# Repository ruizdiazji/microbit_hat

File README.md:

## Placa de expansión para utilizar con MICROBIT    

### Descripción y contexto
---

Esta placa, también llamada "shield" o "hat" en el mundo maker, permite tener acceso a todos los pines de entrada salida de la micro:bit. Además tiene incorporado un IC que permite cargar de forma autónoma una celda 18650 de ion-litio, 10 leds programables ws2812, display oled ssd1306, salida de audio, monitoreo del nivel de batería y un conector que hace muy fácil insertar la placa micro:bit.

micro:bit es una placa programable diseñada para hacer que los niños puedan aprender a programar de una forma amigable y divertida. Entre sus principales socios fundadores se encuentran; BBC, Microsoft, ARM, Lancaster University,British Council, The Institution of Engineering and Technology...(https://archive.microbit.org/es/about/)

### Guía de usuario
---
La placa está desarrollada utilizando el software Kicad, en su versión 5.1.5. Es de doble faz y permite visualizar, el display de pixels led propio de la microbit junto con un display oled ssd1306 y 10 leds ws2812 programables. Está pensada para ser alimentada por su propio conector microUSB (sin necesidad de usar el nativo de la microbit) teniendo así la posibilidad de contar con una alimentación de 3.3v y una corriente máxima de 600mA y, simultaneamente, una recarga automática de la bateria.

Todos los ejemplos disponibles en la web de microbit -makecode.microbit.org- pueden utilizarse con esta placa. Para ello se debe desconectar la micro:bit de la placa de expansión, programarla siguiendo las instrucciones detalladas en la web, luego desconectar el cable USB de la placa microbit e insertar esta en el conector de 40 pines. La forma correcta de colocar la micro:bit en la placa de expansión es la que permite visualizar en una cara el display de leds y, en la cara opuesta, el display oled ssd1306. Una vez se conecte correctamente, se puede alimentar la placa mediante el conector microUSB de la placa de expansión y deslizar la tecla de encendido a la posición de ON, o bien, si no disponemos de una fuente de alimentación USB, se puede energizar con la celda de ion-litio 18650. La conmutación entre fuentes de energía se realiza de forma automática. 
 	
### Guía de instalación
---
En este repositorio se pueden encontar todos los archivos diseñados en Kicad 5.1.5. También hay una carpeta con los gerbers ya listos para fabricación.

#### Dependencias
---
En la carpeta kicad_libraries se puede encontar la librería que diseñe para el conector de 40 pines cylconn. Allí están el footprint, el modelo 3d y el simbolo.
También utilice las siguientes librerías;

CONECTOR MICRO USB: 
                    [Footprint](https://raw.githubusercontent.com/choryuidentify/USB-Micro-B-Unknown-5s-SMT/master/images/footprint.png)

                    [3D Footprint](https://raw.githubusercontent.com/choryuidentify/USB-Micro-B-Unknown-5s-SMT/master/images/footprint_3d.png)

                    [Datasheet](https://raw.githubusercontent.com/choryuidentify/USB-Micro-B-Unknown-5s-SMT/master/datasheet.pdf)

DISPLAY OLED SSD1306: 
                    https://github.com/MichMich/KiCad-SSD1306_OLED-0.91-128x32.git

### Autor/es
---
Ruiz Díaz, Juan Ignacio. Ingeniero Electrónico. 
Email:ruizdiazji@gmail.com

### Información adicional
---
Para el ejemplo que se puede observar en una de las fotos, donde el display oled muestra el logo de micro:bit uitilice el código en micropython y la librería que se detalla en https://www.littlebird.com.au/a/how-to/81/0-96-oled-screen-with-micro-bit.

Si te interesa probar los distintos sensores y periféricos que tiene la placa micro:bit utilizando el lenguaje micropython, en la página https://microbit-challenges.readthedocs.io/en/latest/index.html, podes encontrar documentación muy bien detallada.

### Licencia 
---
[LICENCIA] https://github.com/ruizdiazji/microbit_hat/blob/master/LICENSE.md

Si desconoces qué tipos de licencias existen, podes visitar la página https://choosealicense.com/.

## Limitación de responsabilidades

El autor no será responsable, bajo circunstancia alguna, de daño ni indemnización, moral o patrimonial; directo o indirecto; accesorio o especial; o por vía de consecuencia, previsto o imprevisto, que pudiese surgir:

i. Bajo cualquier teoría de responsabilidad, ya sea por contrato, infracción de derechos de propiedad intelectual, negligencia o bajo cualquier otra teoría; y/o

ii. A raíz del uso de esta placa, incluyendo, pero sin limitación de potenciales defectos en el hardware o software, o la pérdida o inexactitud de los datos de cualquier tipo. Lo anterior incluye los gastos o daños asociados a fallas de comunicación y/o fallas de funcionamiento de hardware, vinculados con la utilización de esta placa

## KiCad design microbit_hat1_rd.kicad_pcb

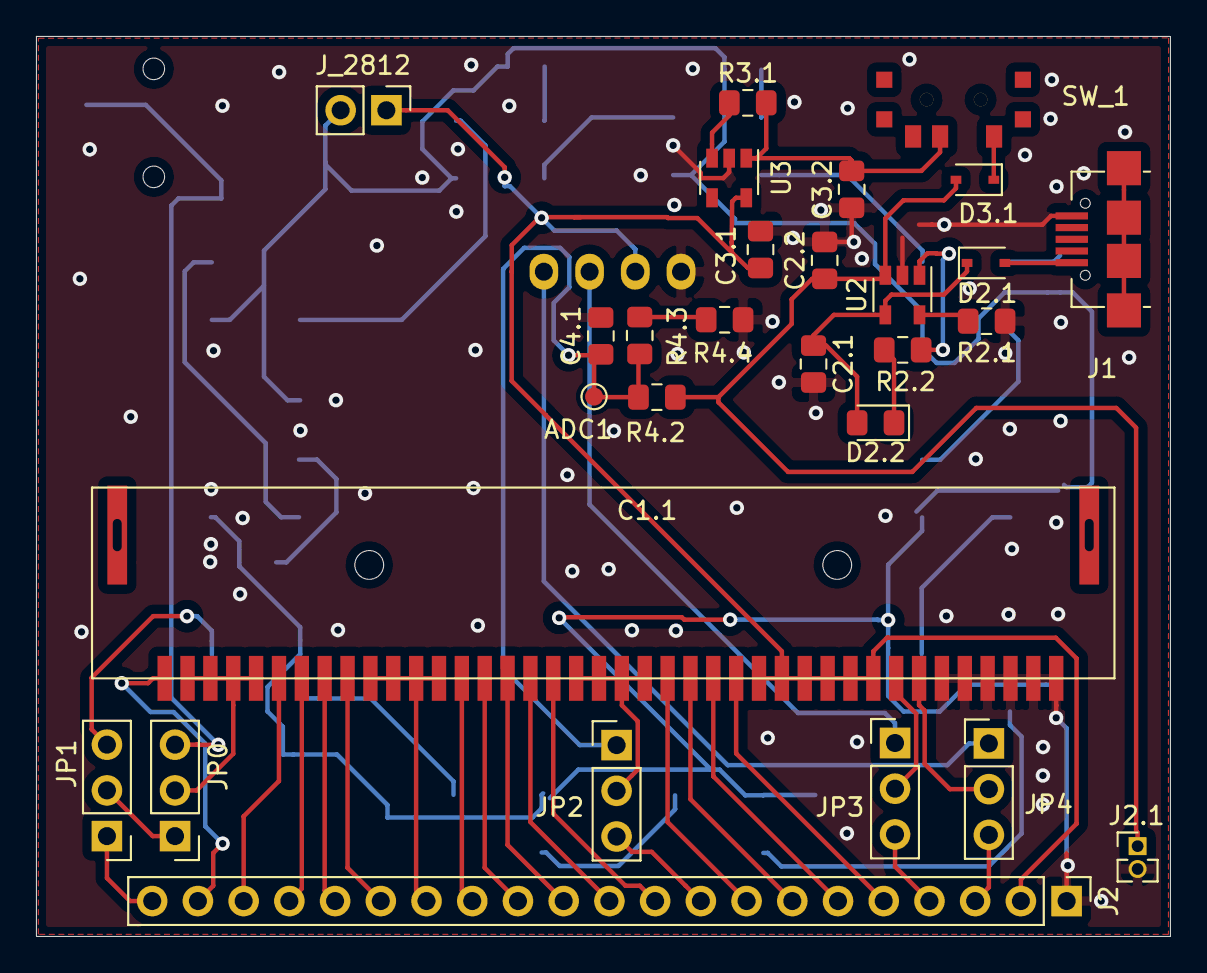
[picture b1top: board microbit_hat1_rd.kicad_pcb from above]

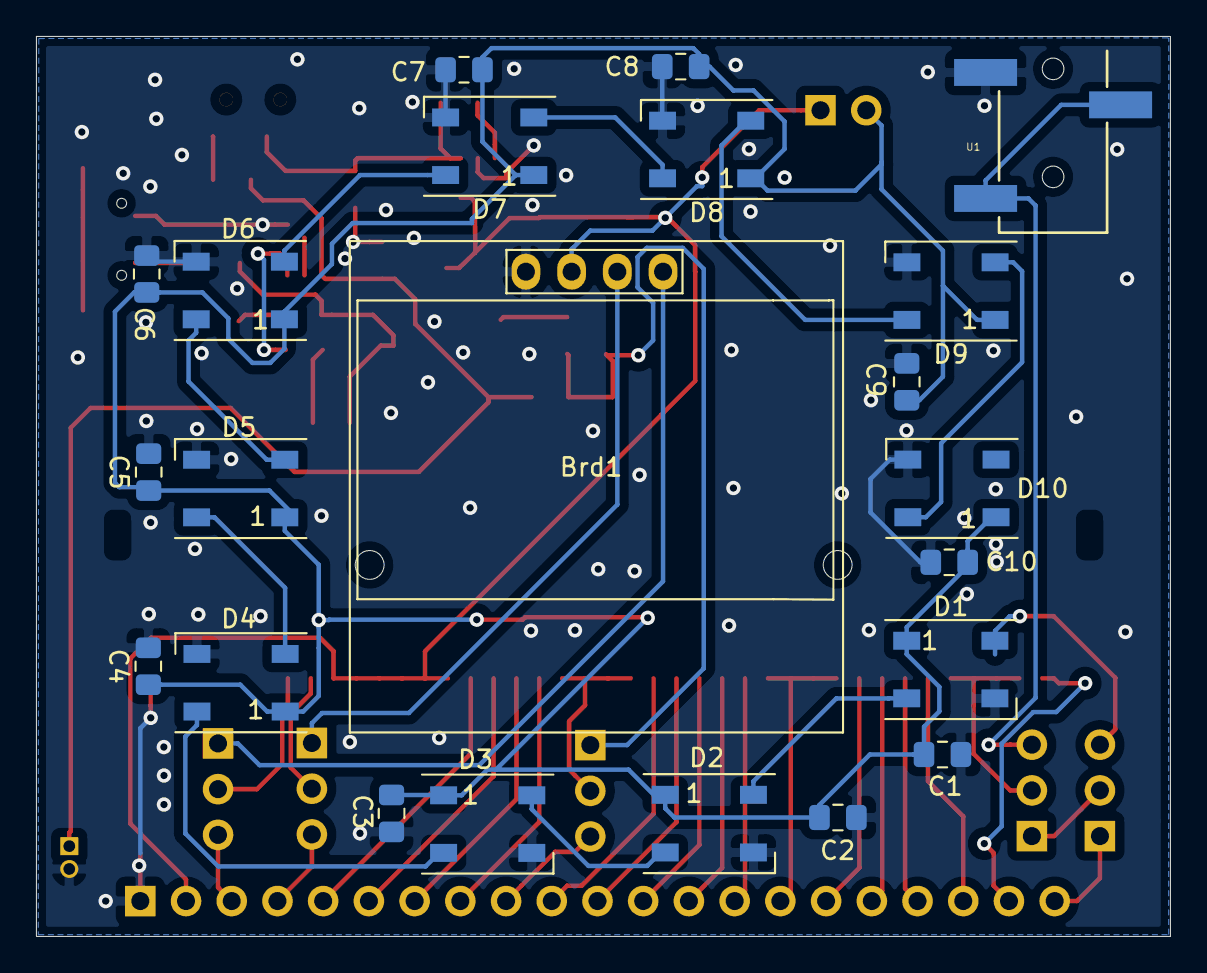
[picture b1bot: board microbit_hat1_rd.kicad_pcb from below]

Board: 2 copper layers, 63.0 x 50.0 mm, 50 parts (22 on the bottom side), 51 nets.

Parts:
ADC1: adc_b; TestPoint_Pad_D1.0mm
Brd1: SSD1306; 128x64OLED
C1, C2, C3, C4, C5, C6, C7, C8, C9, C10: 0.1uF; C_0805_2012Metric_Pad1.15x1.40mm_HandSolder
C1.1: cylconn
C2.1, C2.2: 4.7uF; C_0805_2012Metric_Pad1.15x1.40mm_HandSolder
C3.1, C3.2: 1uF; C_0805_2012Metric_Pad1.15x1.40mm_HandSolder
C4.1: 1nF; C_0805_2012Metric_Pad1.15x1.40mm_HandSolder
D1, D2, D3, D4, D5, D6, D7, D8, D9, D10: WS2812B; LED_WS2812B_PLCC4_5.0x5.0mm_P3.2mm
D2.1, D3.1: BAT60A; D_SOD-323
D2.2: LED; LED_0805_2012Metric_Pad1.15x1.40mm_HandSolder
J1: USB_B_Micro; USB_Micro-B_Unknown_5s_SMT
J2: Conn_01x20_Male; PinHeader_1x21_P2.54mm_Vertical
J2.1: battery; PinHeader_1x02_P1.27mm_Vertical
JP0, JP1, JP2, JP3, JP4: Jumper_NC_Dual; PinHeader_1x03_P2.54mm_Vertical
J_2812: Conn_01x02_Male; PinHeader_1x02_P2.54mm_Vertical
R2.1, R3.1: 10K; R_0805_2012Metric_Pad1.15x1.40mm_HandSolder
R2.2: 470; R_0805_2012Metric_Pad1.15x1.40mm_HandSolder
R4.2: 800k; R_0805_2012Metric_Pad1.15x1.40mm_HandSolder
R4.3, R4.4: 1M; R_0805_2012Metric_Pad1.15x1.40mm_HandSolder
SW_1: SW_DPST_x2; sw_slide_7x3
U1: PJ-320B; 3.5mm_stereo_jack_PJ320B
U2: MCP73831-2-OT; SOT-23-5
U3: AP2112K-3.3; SOT-23-5

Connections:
LED: D1.4, JP1.3
MISO: C1.1.24, J2.7
MOSI: C1.1.25, J2.6
unnamed: C1.1, C2.1, C3.1, C4.1, C5.1, C6.2, C7.2, C8.2, C9.2, C10.2, D1.1, D2.1, D3.1, D4.1, D5.1, D6.1, D7.1, D8.1, D9.1, D10.1, J_2812.2
unnamed: C1.1.2, C1.1.3, C1.1.4, C1.1.5, JP0.2
unnamed: C1.1.19, C1.1.20, C1.1.21, C1.1.22, JP2.2
unnamed: C1.1.33, JP3.2
unnamed: C1.1.34, JP4.2
unnamed: C2.1.1, D2.1.1, D2.2.2, U2.4
unnamed: C3.2.1, R3.1.2, SW_1.2, U3.1
unnamed: D1.2, D2.4
unnamed: D2.2, D3.4
unnamed: D2.2.1, R2.2.1
unnamed: D3.2, D4.4
unnamed: D3.1.1, SW_1.1
unnamed: D4.2, D5.4
unnamed: D5.2, D6.4
unnamed: D6.2, D7.4
unnamed: D7.2, D8.4
unnamed: D8.2, D9.4
unnamed: D9.2, D10.4
unnamed: JP0.1, JP1.2
unnamed: JP0.3, U1.2, U1.3
unnamed: R2.1.1, U2.5
unnamed: R2.2.2, U2.1
unnamed: R3.1.1, U3.3
unnamed: R4.3.2, R4.4.1
P0: J2.21, JP1.1
P1: C1.1.10, C1.1.11, C1.1.12, C1.1.13, J2.15
P2: J2.9, JP2.3
P3: C1.1.1, J2.20
P4: C1.1.6, J2.19
P5: C1.1.7, J2.18
P6: C1.1.8, J2.17
P7: C1.1.9, J2.16
P8: C1.1.14, J2.14
P9: C1.1.15, J2.13
P10: C1.1.16, J2.12
P11: C1.1.17, J2.11
P12: C1.1.18, J2.10
P16: C1.1.26, J2.5
P19: J2.4, JP3.3
P20: J2.3, JP4.3
SCK: C1.1.23, J2.8
SCL: Brd1.3, JP3.1
SDA: Brd1.4, JP4.1
Vbat+: C2.2.1, D3.1.2, J2.1.1, R4.2.1, U2.3
Vdd: Brd1.2, C1.1.27, C1.1.28, C1.1.29, C1.1.30, C1.1.31, C1.1.32, C3.1.1, J2.2, J_2812.1, U3.5
Vin: D2.1.2, J1.1
Vss: Brd1.1, C1.2, C1.1.35, C1.1.36, C1.1.37, C1.1.38, C1.1.39, C1.1.40, C2.2, C2.1.2, C2.2.2, C3.2, C3.1.2, C3.2.2, C4.2, C4.1.2, C5.2, C6.1, C7.1, C8.1, C9.1, C10.1, D1.3, D2.3, D3.3, D4.3, D5.3, D6.3, D7.3, D8.3, D9.3, D10.3, J1.5, J2.1, J2.1.2, R2.1.2, R4.4.2, U1.1, U2.2, U3.2
adc_bat: ADC1.1, C4.1.1, JP2.1, R4.2.2, R4.3.1

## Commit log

2020-03-24 placa de expansion para micro:bit v1.0.0
2020-03-24 redimensionado de imagenes de muestra
2020-03-24 modificacion ruta para imagen de muestra en readme
2020-03-24 cambio en la imagen de muestra sin link en readme
2020-03-25 placa de expansion para microbit
